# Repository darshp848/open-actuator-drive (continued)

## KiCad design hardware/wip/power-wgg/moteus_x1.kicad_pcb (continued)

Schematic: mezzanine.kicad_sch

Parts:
J_STACK1: DF40C-80DP-0.4V(51); Hirose_DF40C-80DP-0.4V_2x40-1MP_P0.4mm; MPN DF40C-80DP-0.4V(51)

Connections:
+3V: J_STACK1.73 (+3V), J_STACK1.75 (+3V), J_STACK1.76 (+3V), J_STACK1.77 (+3V); also elsewhere on the board
+5V: J_STACK1.53 (+5V), J_STACK1.54 (+5V), J_STACK1.55 (+5V), J_STACK1.56 (+5V); also elsewhere on the board
BRAKE_MON: J_STACK1.48 (BRAKE_MON)
CAN_H: J_STACK1.51 (CAN_H); also elsewhere on the board
CAN_L: J_STACK1.52 (CAN_L); also elsewhere on the board
ENC_OUTPUT_CS: J_STACK1.80 (ENC_OUTPUT_CS); also elsewhere on the board
ENC_ROTOR_CS: J_STACK1.30 (ENC_ROTOR_CS); also elsewhere on the board
ENC_SPI_MISO: J_STACK1.28 (ENC_SPI_MISO); also elsewhere on the board
ENC_SPI_MOSI: J_STACK1.29 (ENC_SPI_MOSI); also elsewhere on the board
ENC_SPI_SCK: J_STACK1.27 (ENC_SPI_SCK); also elsewhere on the board
GND: J_STACK1.3 (GND), J_STACK1.4 (GND), J_STACK1.6 (GND), J_STACK1.7 (GND), J_STACK1.10 (GND), J_STACK1.11 (GND), J_STACK1.14 (GND), J_STACK1.15 (GND), J_STACK1.18 (GND), J_STACK1.19 (GND), J_STACK1.22 (GND), J_STACK1.23 (GND), J_STACK1.25 (GND), J_STACK1.26 (GND), J_STACK1.31 (GND), J_STACK1.32 (GND), J_STACK1.35 (GND), J_STACK1.36 (GND), J_STACK1.39 (GND), J_STACK1.40 (GND), J_STACK1.43 (GND), J_STACK1.44 (GND), J_STACK1.49 (GND), J_STACK1.50 (GND), J_STACK1.57 (GND), J_STACK1.58 (GND), J_STACK1.62 (GND), J_STACK1.64 (GND), J_STACK1.66 (GND), J_STACK1.68 (GND), J_STACK1.72 (GND), J_STACK1.74 (GND), J_STACK1.78 (GND); also elsewhere on the board
/Current Sense/CUR1: J_STACK1.9 (CUR1); also elsewhere on the board
/Current Sense/CUR2: J_STACK1.8 (CUR2); also elsewhere on the board
/Current Sense/CUR3: J_STACK1.5 (CUR3); also elsewhere on the board
/Gate Driver/DRV8323_CS: J_STACK1.67 (DRV8323_CS); also elsewhere on the board
/Gate Driver/DRV8323_FAULT: J_STACK1.46 (DRV8323_FAULT); also elsewhere on the board
/Gate Driver/DRV8323_MISO: J_STACK1.65 (DRV8323_MISO); also elsewhere on the board
/Gate Driver/DRV8323_MOSI: J_STACK1.63 (DRV8323_MOSI); also elsewhere on the board
/Gate Driver/DRV8323_SCLK: J_STACK1.61 (DRV8323_SCLK); also elsewhere on the board
/Gate Driver/MOTOR1: J_STACK1.33 (MOTOR1); also elsewhere on the board
/Gate Driver/MOTOR2: J_STACK1.37 (MOTOR2); also elsewhere on the board
/Gate Driver/MOTOR3: J_STACK1.41 (MOTOR3); also elsewhere on the board
/Gate Driver/MOTOR_ENABLE: J_STACK1.45 (MOTOR_ENABLE); also elsewhere on the board
/Gate Driver/MOTOR_HIZ: J_STACK1.34 (MOTOR_HIZ); also elsewhere on the board
/VT Sense/VBAT_SENSE: J_STACK1.13 (VBAT_SENSE); also elsewhere on the board
/VT Sense/VTEMP_FET: J_STACK1.21 (VTEMP_FET); also elsewhere on the board
/VT Sense/VTEMP_MOT: J_STACK1.24 (VTEMP_MOT); also elsewhere on the board
/aux2/AUX2_C: J_STACK1.79 (AUX2_C); also elsewhere on the board

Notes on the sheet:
Fan functions share AUX2_C and ENC_OUTPUT_CS in the X1 reference. Do not fit R43/R44 with output encoder.
Odd contacts = logical A. Even contacts = logical B. Reserved pins are intentionally NC.
27 SCK / 28 MISO / 29 MOSI / 30 rotor CS now serve power-PCB encoders.
3V3 returns to power-board sensing. 5V feeds logic. Rail budgets and startup sequence remain open.

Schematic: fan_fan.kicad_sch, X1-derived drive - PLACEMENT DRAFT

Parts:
C82: 4.7uF; C_1206_3216Metric; MPN GRJ31CC72A475KE01K
FAN1: Conn_01x04_Pin; PinSocket_2x02_P2.54mm_Vertical; not fitted
R43, R44: 100; R_0402_1005Metric; MPN MF-RES-0402-100; not fitted

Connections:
+12V_GATE: C82.1, FAN1.2; also elsewhere on the board
ENC_OUTPUT_CS: R44.1; also elsewhere on the board
GND: C82.2, FAN1.1; also elsewhere on the board
unnamed: FAN1.3, R44.2
unnamed: FAN1.4, R43.2
/aux2/AUX2_C: R43.1; also elsewhere on the board

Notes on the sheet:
Split draft: original X1 circuit; actuator fit and final routing pending.
FAN1 is DNP. It now sits on +12V_GATE (sized for the gate driver, 100 mA stress): resize that rail before fitting a fan.
DNP FAN1, R43 and R44 with dual encoder configuration. GPIOs are shared.

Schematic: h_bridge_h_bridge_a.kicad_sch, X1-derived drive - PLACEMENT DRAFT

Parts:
C24: 0.1uF 100V; C_1206_3216Metric; MPN 12061C104KAT2A
D4: BAT41KFILM; SOD-523_STM; MPN BAT41KFILM
NT2, NT3: NetTie_2; NetTie-2_SMD_Pad0.2
Q1, Q2: ISC060N10NM6ATMA1; Infineon_PG-TDSON-8-FL_ISC060N10NM6; MPN ISC060N10NM6ATMA1
R14: 1mOhm; R_2512_6332Metric; MPN WSLF25121L000FEA
R51, R52: 2R; R_0603_1608Metric; MPN RC0603FR-072RL
R53, R54: 100k 1%; R_0402_1005Metric; MPN RC0402FR-07100KL
X1: Conn_01x01; POWER_M2.5

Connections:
/H Bridge A/SPX_Q: C24.2, NT2.2, Q2.1 (S), Q2.2 (S), Q2.3 (S), R14.1, R54.2
GNDPWR: D4.2, NT3.2, R14.2; also elsewhere on the board
unnamed: Q1.4 (G), R51.2, R53.1
unnamed: Q2.4 (G), R52.2, R54.1
V+: C24.1, Q1.5 (D); also elsewhere on the board
/Gate Driver/GHA: R51.1; also elsewhere on the board
/Gate Driver/GLA: D4.1, R52.1; also elsewhere on the board
/H Bridge A/OUTX: Q1.1 (S), Q1.2 (S), Q1.3 (S), Q2.5 (D), R53.2, X1.1; also elsewhere on the board
/H Bridge A/SXX_N: NT3.1; also elsewhere on the board
/H Bridge A/SXX_P: NT2.1; also elsewhere on the board

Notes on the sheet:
Split draft: original X1 circuit; actuator fit and final routing pending.

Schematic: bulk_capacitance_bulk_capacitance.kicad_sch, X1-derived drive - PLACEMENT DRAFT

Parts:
C45, C46, C47, C48, C49, C50, C51, C52, C53, C54, C55, C56, C57, C58, C59, C60, C61, C62, C63, C64, C65, C66, C67, C68, C69, C70, C71, C72, C73, C74, C75, C76, C77, C78, C79, C80: 4.7uF 100V; C_1206_3216Metric; MPN GRJ31CC72A475KE01K

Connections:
GNDPWR: C45.2, C46.2, C47.2, C48.2, C49.2, C50.2, C51.2, C52.2, C53.2, C54.2, C55.2, C56.2, C57.2, C58.2, C59.2, C60.2, C61.2, C62.2, C63.2, C64.2, C65.2, C66.2, C67.2, C68.2, C69.2, C70.2, C71.2, C72.2, C73.2, C74.2, C75.2, C76.2, C77.2, C78.2, C79.2, C80.2; also elsewhere on the board
V+: C45.1, C46.1, C47.1, C48.1, C49.1, C50.1, C51.1, C52.1, C53.1, C54.1, C55.1, C56.1, C57.1, C58.1, C59.1, C60.1, C61.1, C62.1, C63.1, C64.1, C65.1, C66.1, C67.1, C68.1, C69.1, C70.1, C71.1, C72.1, C73.1, C74.1, C75.1, C76.1, C77.1, C78.1, C79.1, C80.1; also elsewhere on the board

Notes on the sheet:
Split draft: original X1 circuit; actuator fit and final routing pending.

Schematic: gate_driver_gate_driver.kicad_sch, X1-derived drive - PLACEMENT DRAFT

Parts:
C18: 1uF; C_0603_1608Metric; MPN MF-CAP-0603-1uF
C19: 0.1uF 100V; C_0603_1608Metric; MPN GCJ188R72A104KA01D
C20: 1uF 16V; C_0402_1005Metric; MPN GRM155R61C105KA12D
C21, C22, C88, C89, C90: 1uF 25V; C_0603_1608Metric; MPN C1608X7R1E105K080AE
C85: 10uF 25V; C_0805_2012Metric; MPN GRM21BR61E106KA73L
C86: 1uF 100V; C_0805_2012Metric; MPN GCM21BC72A105KE36L
C87: 0.1uF 25V; C_0402_1005Metric; MPN GCM155R71E104KE02D
Q8: BSS138; SOT-23; MPN BSS138
R12, R13, R48, R49: 10k 1%; R_0402_1005Metric; MPN RC0402FR-0710KL
R50, R72: 100k 1%; R_0402_1005Metric; MPN RC0402FR-07100KL
U5: DRV8363RGZR; VQFN-48-1EP_7x7mm_P0.5mm_EP5.6x5.6mm_RGZ0048D; MPN DRV8363RGZR

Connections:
+3V: C18.1, C87.1, R12.1, R13.1, R48.1, U5.23 (VREF); also elsewhere on the board
+12V_GATE: C85.1, U5.30 (GVDD); also elsewhere on the board
/Gate Driver/ASCIN: R50.1, U5.29 (ASCIN)
/Gate Driver/BSTA: C88.1, U5.36 (BSTA)
/Gate Driver/BSTB: C89.1, U5.45 (BSTB)
/Gate Driver/BSTC: C90.1, U5.46 (BSTC)
/Gate Driver/CPH: C22.1, U5.33 (CPTH)
/Gate Driver/CPL: C22.2, U5.32 (CPTL)
/Gate Driver/DRVOFF: Q8.3 (D), R49.2, U5.9 (DRVOFF)
/Gate Driver/DVDD: C20.1, R49.1, U5.28 (DVDD)
/Gate Driver/NSLEEP: R48.2, U5.21 (nSLEEP)
/Gate Driver/VCP: C21.2, U5.34 (VCP)
GND: C18.2, C20.2, C85.2, C87.2, Q8.2 (S), R50.2, R72.2, U5.10 (AGND), U5.27 (GND); also elsewhere on the board
GNDPWR: C19.2, C86.2, U5.49 (PAD); also elsewhere on the board
V+: C19.1, C21.1, C86.1, U5.35 (VDRAIN); also elsewhere on the board
/Current Sense/CUR1: U5.24 (SOC); also elsewhere on the board
/Current Sense/CUR2: U5.25 (SOB); also elsewhere on the board
/Current Sense/CUR3: U5.26 (SOA); also elsewhere on the board
/Gate Driver/DRV8323_CS: U5.20 (nSCS); also elsewhere on the board
/Gate Driver/DRV8323_FAULT: R13.2, U5.22 (nFAULT); also elsewhere on the board
/Gate Driver/DRV8323_MISO: R12.2, U5.17 (SDO); also elsewhere on the board
/Gate Driver/DRV8323_MOSI: U5.18 (SDI); also elsewhere on the board
/Gate Driver/DRV8323_SCLK: U5.19 (SCLK); also elsewhere on the board
/Gate Driver/GHA: U5.38 (GHA); also elsewhere on the board
/Gate Driver/GHB: U5.43 (GHB); also elsewhere on the board
/Gate Driver/GHC: U5.48 (GHC); also elsewhere on the board
/Gate Driver/GLA: U5.39 (GLA); also elsewhere on the board
/Gate Driver/GLB: U5.42 (GLB); also elsewhere on the board
/Gate Driver/GLC: U5.1 (GLC); also elsewhere on the board
/Gate Driver/MOTOR1: U5.11 (INHA); also elsewhere on the board
/Gate Driver/MOTOR2: U5.13 (INHB); also elsewhere on the board
/Gate Driver/MOTOR3: U5.15 (INHC); also elsewhere on the board
/Gate Driver/MOTOR_ENABLE: Q8.1 (G), R72.1; also elsewhere on the board
/Gate Driver/MOTOR_HIZ: U5.12 (INLA), U5.14 (INLB), U5.16 (INLC); also elsewhere on the board
/H Bridge A/OUTX: C88.2, U5.37 (SHA); also elsewhere on the board
/H Bridge A/SXX_N: U5.4 (SNA); also elsewhere on the board
/H Bridge A/SXX_P: U5.3 (SPA), U5.40 (SLA); also elsewhere on the board
/H Bridge B/OUTX: C89.2, U5.44 (SHB); also elsewhere on the board
/H Bridge B/SXX_N: U5.6 (SNB); also elsewhere on the board
/H Bridge B/SXX_P: U5.5 (SPB), U5.41 (SLB); also elsewhere on the board
/H Bridge C/OUTX: C90.2, U5.47 (SHC); also elsewhere on the board
/H Bridge C/SXX_N: U5.8 (SNC); also elsewhere on the board
/H Bridge C/SXX_P: U5.2 (SLC), U5.7 (SPC); also elsewhere on the board

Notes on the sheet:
GVDD from +12V_GATE (separate gate rail, LT8631 U15 on the Power Input sheet). PAD (thermal) to GNDPWR, AGND/GND to GND (datasheet 7.3.1).
DRV8363 per SLVSHQ3 Table 7-1: CGVDD 10uF, CDVDD 1uF, CCPT_FLY 1uF, CVCP 1uF, RnFAULT 10k, CVREF 0.1uF, CVDRAIN 1uF, CBST 1uF
3x PWM: INHx = PWM, INLx = enable (MOTOR_HIZ). DRVOFF high = outputs off: R49 pulls it to DVDD, Q8 pulls it low only while MOTOR_ENABLE is high (off on +3V loss, reset or unplugged logic). ASCIN pulled low; SPI_ASC_EN is the firmware path (D06).

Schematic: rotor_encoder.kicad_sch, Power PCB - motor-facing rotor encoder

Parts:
C42: 1uF; C_0402_1005Metric; MPN MF-CAP-0402-1uF
C44: 0.1uF; C_0402_1005Metric; MPN MF-CAP-0402-0.1uF
R63: 10k; R_0603_1608Metric; MPN RC0603FR-0710KL
TP6: ROTOR_CAL; TestPoint_Pad_D1.0mm
U7: MT6835GT-STD-R; TSSOP-16_4.4x5mm_P0.65mm; MPN MT6835GT-STD-R

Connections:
+3V: C42.1, C44.1, U7.9 (VDD); also elsewhere on the board
ENC_ROTOR_CAL: R63.1, TP6.1, U7.4 (CAL_EN)
ENC_ROTOR_CS: U7.8 (CSN); also elsewhere on the board
ENC_SPI_MISO: U7.5 (MISO); also elsewhere on the board
ENC_SPI_MOSI: U7.6 (MOSI); also elsewhere on the board
ENC_SPI_SCK: U7.7 (SCK); also elsewhere on the board
GND: C42.2, C44.2, R63.2, U7.11 (TEST), U7.12 (VSS), U7.13 (TEST_EN); also elsewhere on the board

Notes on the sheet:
U7 is now an MT6835 (user decision 2026-10-24), wired like U9: SPI mode 3 shared with the output sensor; CS = ENC_ROTOR_CS (pull-up R47 on the output-encoder sheet).

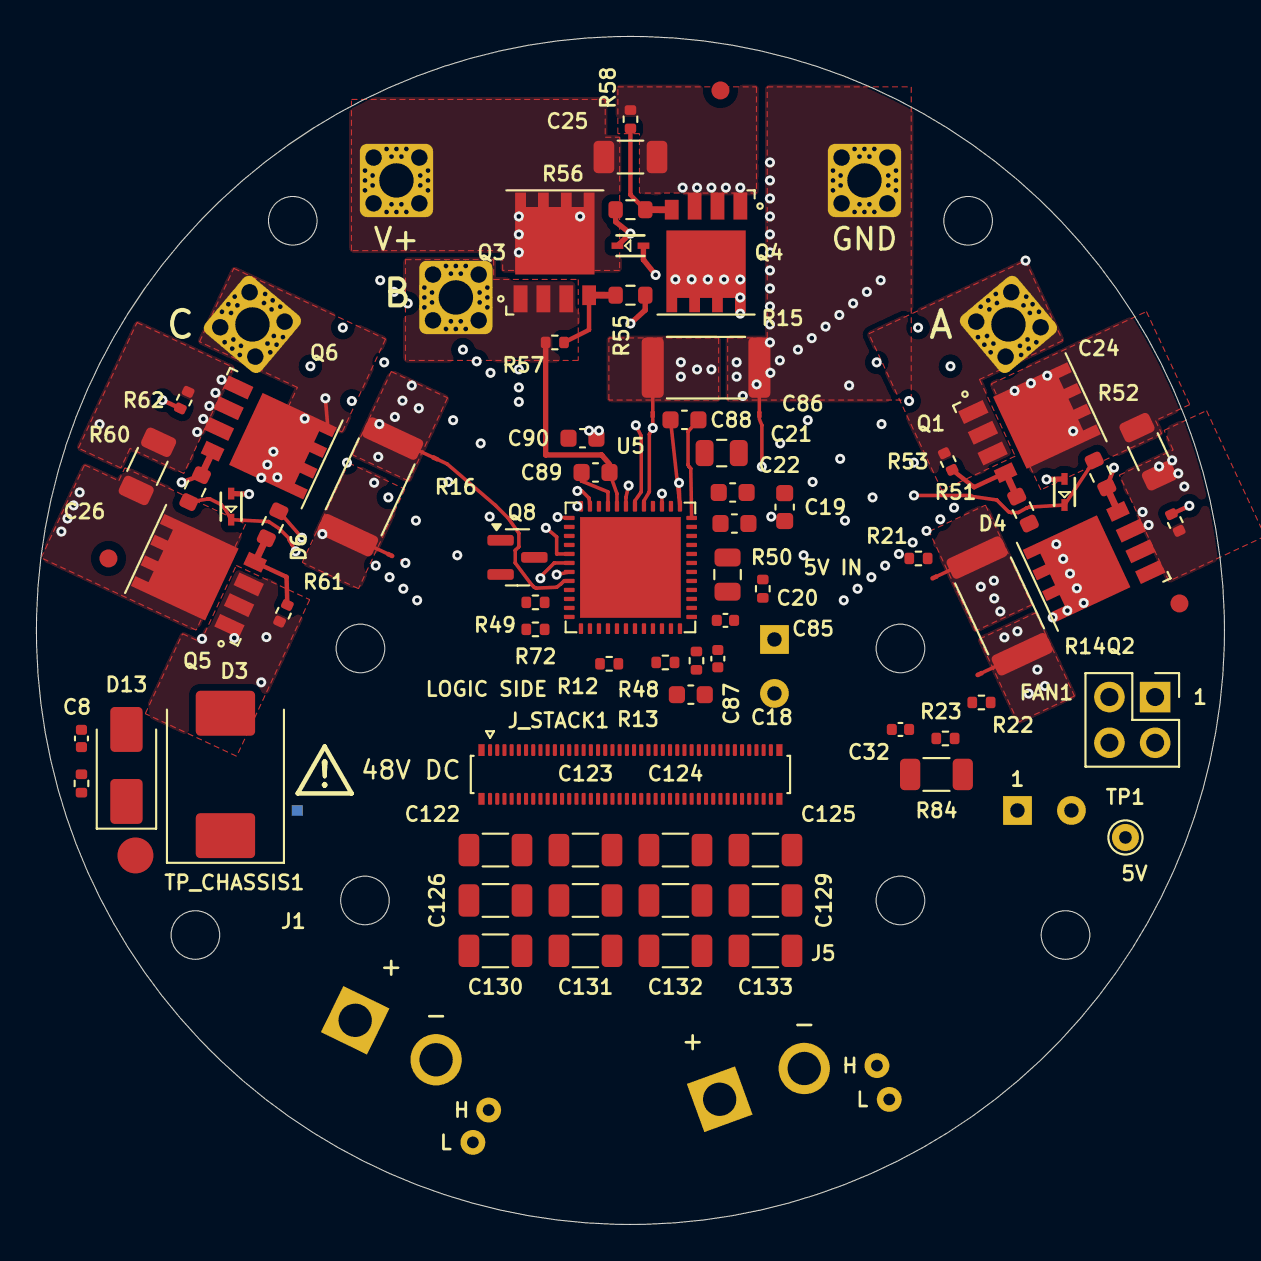
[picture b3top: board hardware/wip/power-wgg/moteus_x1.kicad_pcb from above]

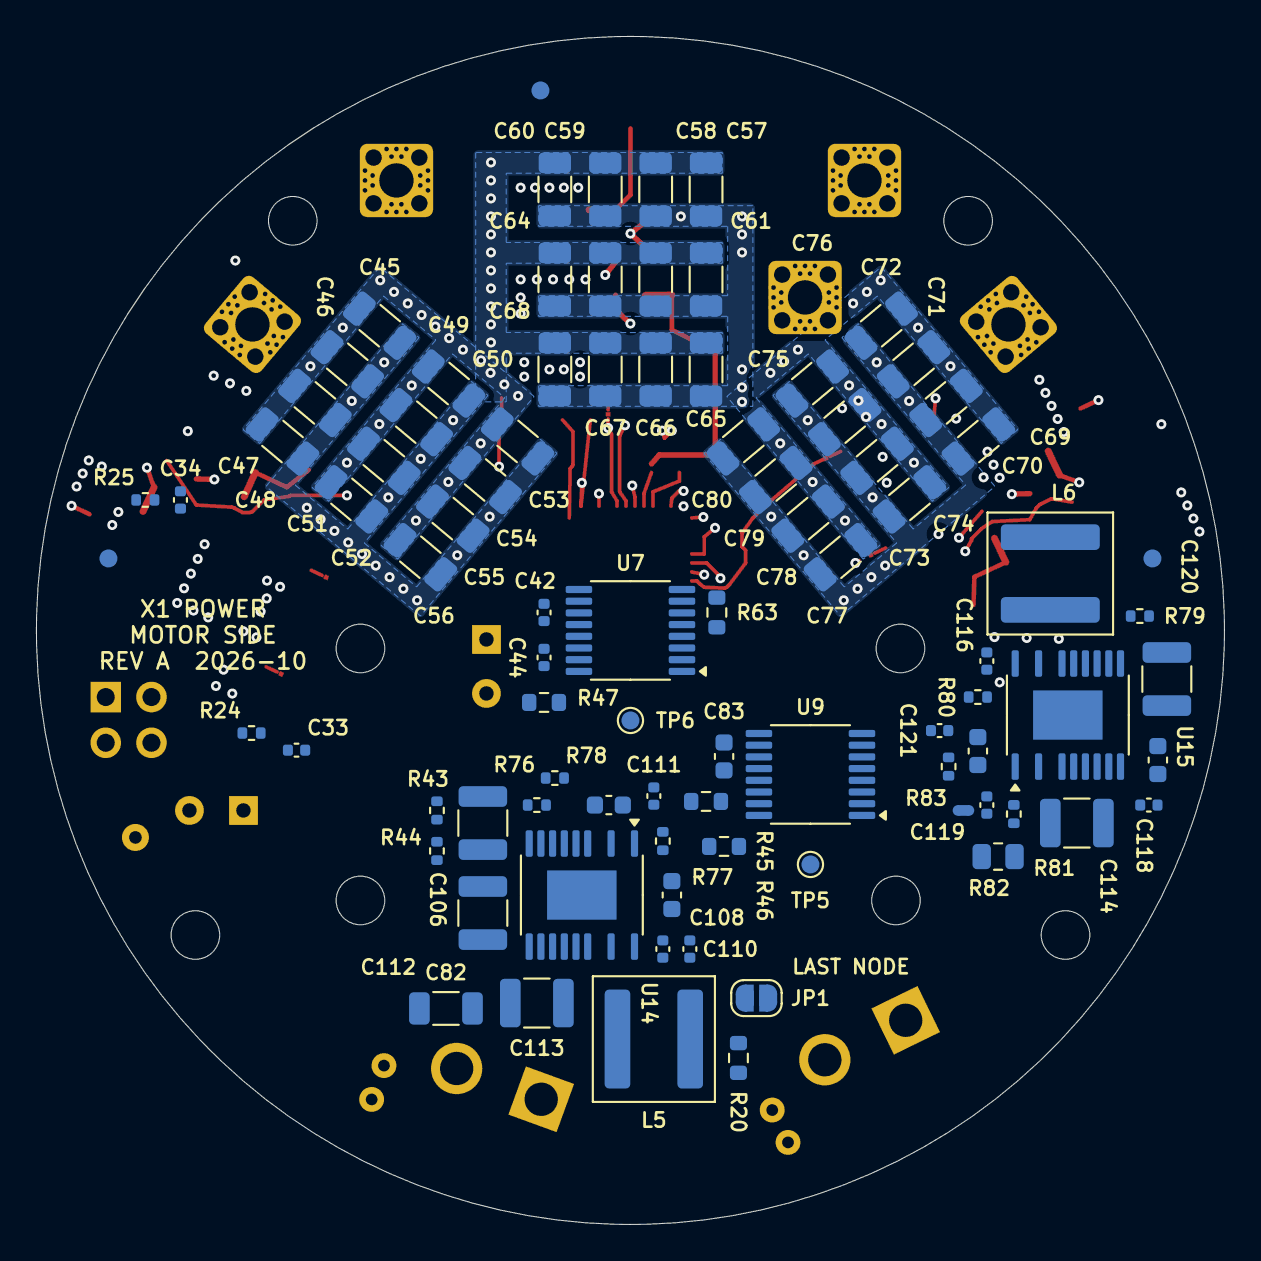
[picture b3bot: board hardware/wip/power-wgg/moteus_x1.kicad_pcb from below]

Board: 6 copper layers, 66.0 x 66.0 mm, 185 parts (88 on the bottom side), 87 nets.

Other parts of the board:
FID_B1, FID_B2, FID_B3: Fiducial_1mm_Mask2mm
FID_F1, FID_F2, FID_F3: Fiducial_1mm_Mask2mm

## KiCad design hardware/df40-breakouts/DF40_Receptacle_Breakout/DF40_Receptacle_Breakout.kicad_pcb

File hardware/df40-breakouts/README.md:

# X1 stack DF40 breakouts

Two bench breakouts for the X1 two-story stack. The stack has one
board-to-board connector, J_STACK1, a Hirose DF40 80-contact pair at 0.4 mm
pitch:

| Board | Part | Side |
| --- | --- | --- |
| Common_Logic | DF40HC(3.0)-80DS-0.4V receptacle | bottom |
| Power_Reference (WGG) and Power_P96 | DF40C-80DP-0.4V header | top |

The other connectors in the X1 projects (XT30/XT90, JST GH/ZR/PH, 1.27 and
2.54 mm pin headers) are cable or debug connectors, not mezzanines.

No off-the-shelf DF40 80-pin to 0.1" breakout was found (2026-11-01 search:
distributor listings, Tindie, OSH Park; the only DF40 breakout found is a
30-pin OSH Park project), so these are custom.

## The boards

| Project | Connector | Use |
| --- | --- | --- |
| `DF40_Header_Breakout` | DF40C-80DP-0.4V on top | The logic board plugs onto it exactly as it plugs onto a power board. Bring up or probe the logic board alone. |
| `DF40_Receptacle_Breakout` | DF40HC(3.0)-80DS-0.4V on the bottom | Plugs onto a power board in place of the logic board. Drive or probe a power board from a bench MCU. |

Every DF40 contact gets one 0.1" through-hole point. J2 (2x20) carries the odd
row and J3 (2x20) the even row: J2 pin k is DF40 pin 2k-1 and J3 pin k is DF40
pin 2k. Each pin is labelled on the silkscreen with its DF40 pin number and net.
[`pinout.json`](pinout.json) has the full map.

Mechanical fit:

- The connector uses the stack boards' own land patterns (copied into
  `X1_Breakout.pretty`), at the same position, side and orientation as the board
  it stands in for. The generator asserts pad 1 lands where it does on the stack.
- H1/H2 are the two spacer positions common to all three stack boards
  ((135,115) and (165,115) in stack coordinates). With 3 mm spacers there they
  fix orientation, so the DF40 cannot be mated 180 degrees out. The other stack
  holes sit in the fan-out and are omitted; remove those spacers first.
- Near the connector the outline stays inside the logic board's footprint and
  clears P96's 5V IN pads. It covers P96's FAN1 socket, as the logic board
  itself does; that clash is open on the stack and both fit once FAN1 moves.
- The headers sit at least 2 mm beyond the rim of both power boards, so no
  through-hole pin lands over a power board. The tongue that crosses the rim
  rides 3 mm above the power board. Checked against P96 and Power_Reference:
  only parts under 2.6 mm tall are under it. Re-check this for any new power
  board.

Electrical:

- 2 layers, 1.6 mm, about 100 x 80 mm, ground pour on both sides. The even
  DF40 row fans out below the connector to two staggered via rows, so no via
  sits at the 0.4 mm pitch. All bends are 45 degrees. About 330 tented
  0.6/0.3 mm stitching vias on a 2.5 mm grid tie the two ground pours together
  wherever the pour has room on both layers.
- Every rule is inside JLCPCB's standard 2-layer process with no surcharge
  (jlcpcb.com/capabilities/pcb-capabilities, read 2026-11-02): trace/space
  0.127/0.127 mm (limit 0.10), vias 0.6/0.3 mm (0.15 mm annular ring), via hole
  to track at least 0.2 mm, copper to edge 0.3 mm (limit 0.2), silkscreen text
  1.0 mm with 0.17 mm lines. KiCad's DRC rules are set to these values.
- Signal integrity (hand estimates): with no plane under the 0.4 mm-pitch
  buses, neighbouring traces couple about 24% near-end to a ~1 ns edge. Near-end
  crosstalk scales with how much of the edge fits in the ~0.5-1 ns of coupled
  length, so with 10 ns edges it falls to roughly 2-3% (under 0.1 V from a
  3.3 V signal). Drive these lines with the STM32 GPIO speed set to low or
  medium and keep SPI to a few MHz. Every analog line (CUR1-3, VBAT_SNS,
  VTEMP_*) has GND traces on both sides; the signal-to-signal neighbours are
  the DRV SPI group, ENC_SCK/MOSI, ENC_MISO/ROT_CS, DRV_FAULT/BRAKE_MON and
  CAN_H/CAN_L next to +5V. No line needs controlled impedance. A four-layer design with ground inner layers was estimated at about 5% coupling.
- The four +5V and four +3V contacts are tied together between the DF40 pad
  rows, as they are on the stack boards. Each contact is rated 0.3 A, and each
  0.127 mm trace carries about the same, so keep each rail under about 1 A
  through the breakout.
- Reserved contacts (`RSV_*`) are broken out but are unconnected on the stack
  boards today.

## Status

KiCad 10.0 DRC: 0 violations, 0 unconnected, schematic parity clean. ERC:
0 violations. Not fabricated, not mated with real parts, and not yet run
through JLCPCB's online DFM check.

[Header Gerber and drill ZIP](../../fab/df40-breakouts/DF40_Header_Breakout/DF40_Header_Breakout-gerbers.zip)
and [receptacle Gerber and drill ZIP](../../fab/df40-breakouts/DF40_Receptacle_Breakout/DF40_Receptacle_Breakout-gerbers.zip).
The design uses a two-layer, 1.6 mm stackup. Review the [fabrication notes](../../fab/)
and [parts list](bom.csv) before preparing an order.

The breakouts inherit the stack's open item: DF40 pad numbering versus Hirose's
mating view has not been checked against the datasheet. They copy the stack
footprints exactly, so they agree with the stack whichever way that resolves.

## Regenerating

```
"%LOCALAPPDATA%/Programs/KiCad/10.0/bin/python.exe" generate.py
```

[`generate.py`](generate.py) reads J_STACK1 from the three stack boards, fails if
their pinouts disagree, and rewrites both breakout projects in place. Run it in a disposable checkout to compare
its outputs. It only reads the stack
boards. Routing is generated by the script; Freerouting could not escape the
0.4 mm pitch.

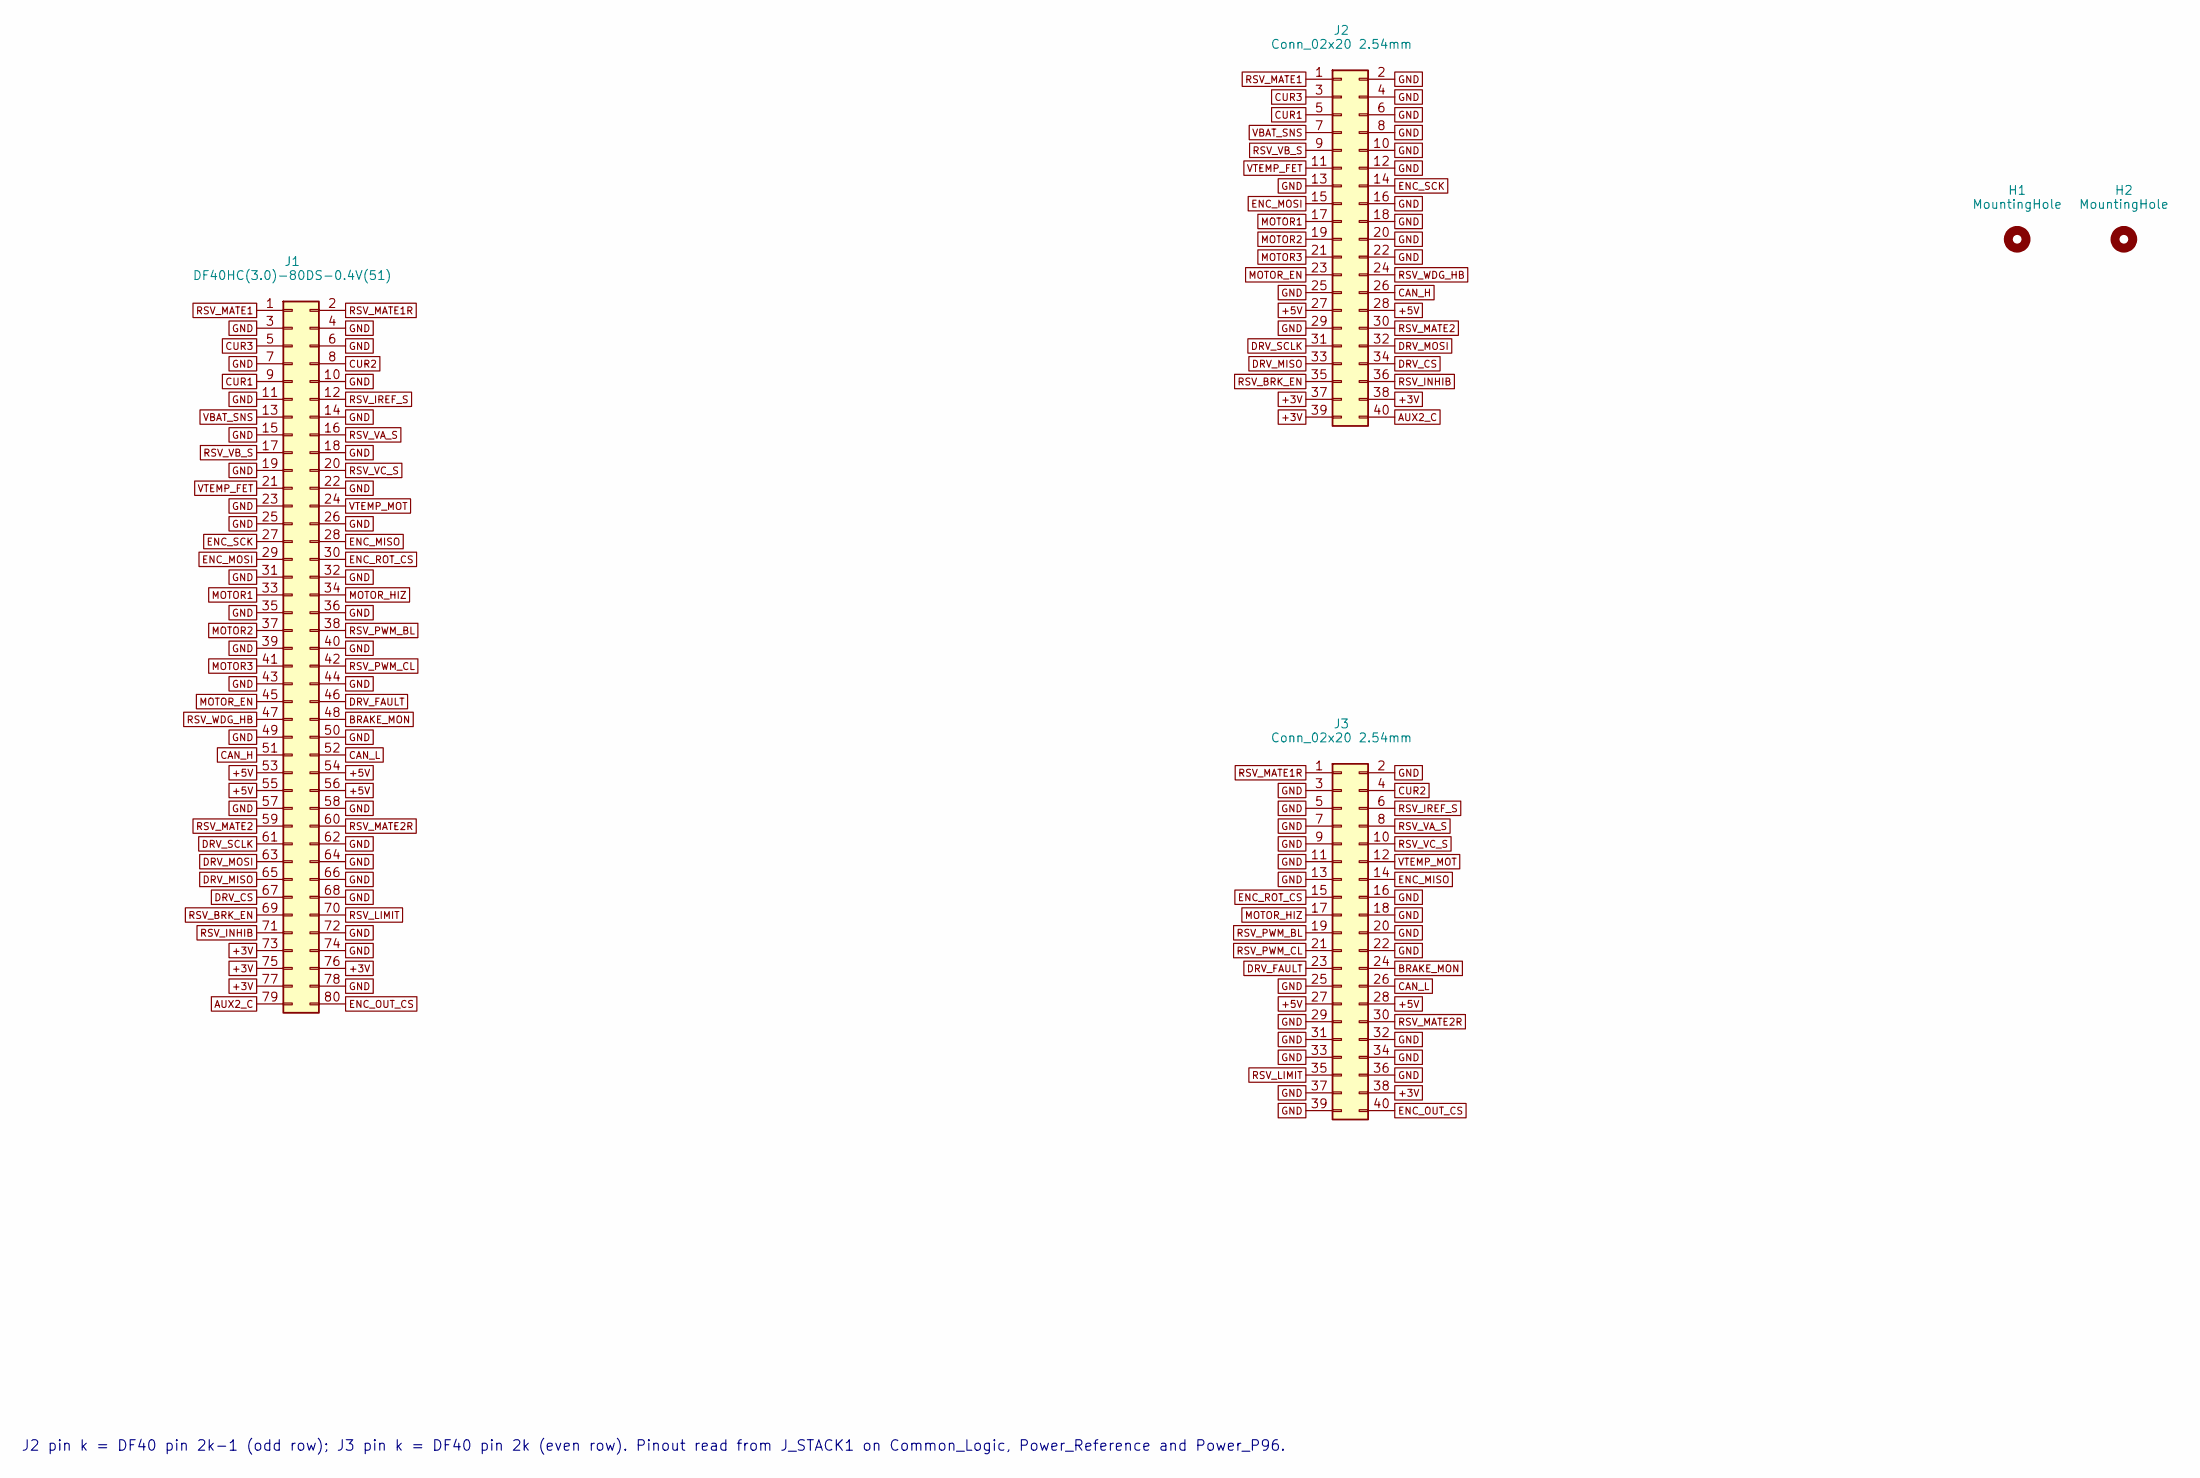
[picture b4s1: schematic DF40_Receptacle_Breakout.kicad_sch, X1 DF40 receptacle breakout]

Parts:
H1, H2: MountingHole; MountingHole_2.7mm_M2.5
J1: DF40HC(3.0)-80DS-0.4V(51); Hirose_DF40HC(3.0)-80DS-0.4V_2x40_P0.4mm
J2, J3: Conn_02x20 2.54mm; PinHeader_2x20_P2.54mm_Vertical

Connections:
+3V: J1.73, J1.75, J1.76, J1.77, J2.37, J2.38, J2.39, J3.38
+5V: J1.53, J1.54, J1.55, J1.56, J2.27, J2.28, J3.27, J3.28
AUX2_C: J1.79, J2.40
BRAKE_MON: J1.48, J3.24
CAN_H: J1.51, J2.26
CAN_L: J1.52, J3.26
CUR1: J1.9, J2.5
CUR2: J1.8, J3.4
CUR3: J1.5, J2.3
DRV_CS: J1.67, J2.34
DRV_FAULT: J1.46, J3.23
DRV_MISO: J1.65, J2.33
DRV_MOSI: J1.63, J2.32
DRV_SCLK: J1.61, J2.31
ENC_MISO: J1.28, J3.14
ENC_MOSI: J1.29, J2.15
ENC_OUT_CS: J1.80, J3.40
ENC_ROT_CS: J1.30, J3.15
ENC_SCK: J1.27, J2.14
GND: J1.3, J1.4, J1.6, J1.7, J1.10, J1.11, J1.14, J1.15, J1.18, J1.19, J1.22, J1.23, J1.25, J1.26, J1.31, J1.32, J1.35, J1.36, J1.39, J1.40, J1.43, J1.44, J1.49, J1.50, J1.57, J1.58, J1.62, J1.64, J1.66, J1.68, J1.72, J1.74, J1.78, J2.2, J2.4, J2.6, J2.8, J2.10, J2.12, J2.13, J2.16, J2.18, J2.20, J2.22, J2.25, J2.29, J3.2, J3.3, J3.5, J3.7, J3.9, J3.11, J3.13, J3.16, J3.18, J3.20, J3.22, J3.25, J3.29, J3.31, J3.32, J3.33, J3.34, J3.36, J3.37, J3.39
MOTOR1: J1.33, J2.17
MOTOR2: J1.37, J2.19
MOTOR3: J1.41, J2.21
MOTOR_EN: J1.45, J2.23
MOTOR_HIZ: J1.34, J3.17
RSV_BRK_EN: J1.69, J2.35
RSV_INHIB: J1.71, J2.36
RSV_IREF_S: J1.12, J3.6
RSV_LIMIT: J1.70, J3.35
RSV_MATE1: J1.1, J2.1
RSV_MATE1R: J1.2, J3.1
RSV_MATE2: J1.59, J2.30
RSV_MATE2R: J1.60, J3.30
RSV_PWM_BL: J1.38, J3.19
RSV_PWM_CL: J1.42, J3.21
RSV_VA_S: J1.16, J3.8
RSV_VB_S: J1.17, J2.9
RSV_VC_S: J1.20, J3.10
RSV_WDG_HB: J1.47, J2.24
VBAT_SNS: J1.13, J2.7
VTEMP_FET: J1.21, J2.11
VTEMP_MOT: J1.24, J3.12

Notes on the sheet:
J2 pin k = DF40 pin 2k-1 (odd row); J3 pin k = DF40 pin 2k (even row). Pinout read from J_STACK1 on Common_Logic, Power_Reference and Power_P96.

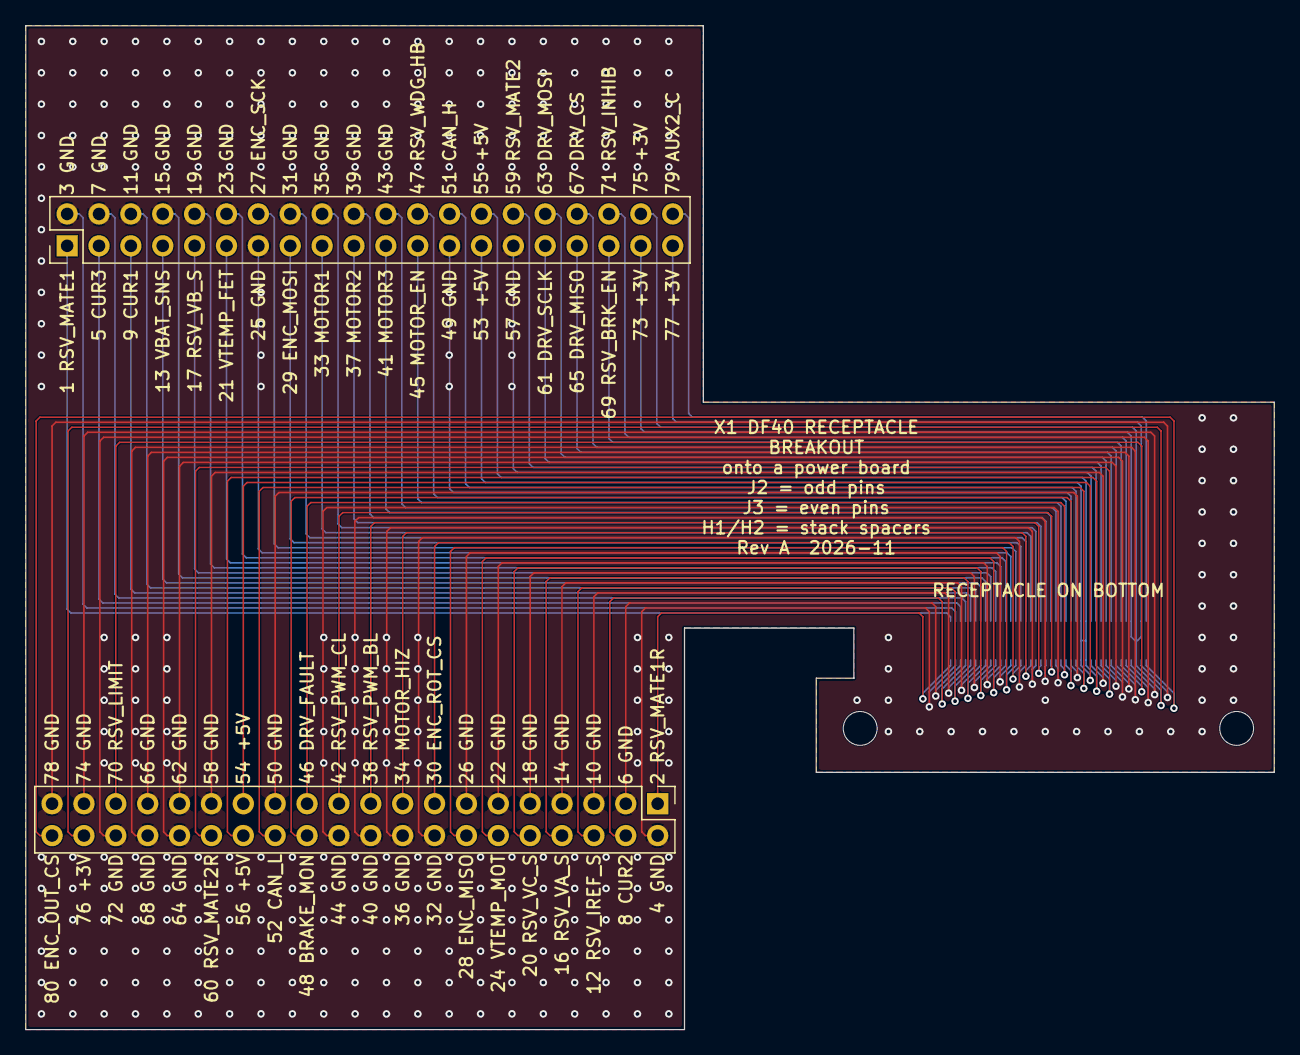
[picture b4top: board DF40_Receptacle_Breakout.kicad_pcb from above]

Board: 2 copper layers, 99.5 x 80.0 mm, 5 parts (1 on the bottom side), 42 nets.

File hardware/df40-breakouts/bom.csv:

Board,Ref,Qty per board,Manufacturer,MPN,DigiKey PN,DigiKey stock 2026-11-02,Unit price (qty 1)
DF40_Header_Breakout,J1,1,Hirose,DF40C-80DP-0.4V(51),cut tape (search MPN),25224,$1.93
DF40_Receptacle_Breakout,J1,1,Hirose,DF40HC(3.0)-80DS-0.4V(51),26-DF40HC(3.0)-80DS-0.4V(51)CT-ND,4743,$3.13
Both,J2 J3,2,Sullins,PRPC020DAAN-RC,35-PRPC020DAAN-RC-ND,5823,$0.95

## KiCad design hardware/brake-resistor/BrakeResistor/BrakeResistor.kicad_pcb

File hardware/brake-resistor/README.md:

# X1 brake resistor board (rev B)

The 2.5 ohm load for the [support board](../support-board/)'s brake chopper.
The current Rev B layout is a 190 × 38 mm strip with four heatsinks in one row.

## What it is

| | |
|---|---|
| Bank | 4 x Vishay LTO100 10 ohm in parallel = 2.5 ohm (same value the support board and system model assume) |
| Cooling | Each resistor screwed to its own Ohmite RA-T2X-64E board-level heatsink (3.1 C/W natural), with silicone grease |
| Thermostat | Sensata Airpax 67L085P, normally closed, opens at 85 +/- 5 C. Its bracket is plastic, so it is isolated. It shares R4's M3 screw on the far face of HS4's web. |
| J1 | Two 2.0 mm wire pads, 8 mm pitch, the same land as support J4. 1 = BUS+, 2 = BRK_SW. Use a 16 AWG pair. |
| J2 | JST PH 2-pin to support J6 (PH to PH lead). 1 = TH_OPEN, 2 = support GND. |
| PCB | 190 × 38 mm, 2 layers, 1.6 mm, 1 oz nominal. BUS+ is a plane on top and BRK_SW a plane on the bottom, so the chopper loop is two parallel plates. |
| Cost | About $62 in parts for one board at qty 1 (see [bom.csv](bom.csv); all in stock at DigiKey on 2026-11-02) plus the PCB |

Mount the board flat with the heatsink fins vertical. The heatsinks have a nominal
4 mm gap between adjacent end fins. The five M3 holes and both connectors sit
along the long edge.

## Thermal sizing for the earlier layout

[brake_sizing.py](brake_sizing.py) models the earlier two-by-two heatsink layout. Its output is in
[checks/brake_sizing-output.txt](checks/brake_sizing-output.txt).

The strip's smaller gaps change airflow. The estimates below have no hardware
validation and do not establish ratings for the strip.

The model puts 1.3 kW across the bank while the chopper conducts. Each burst lasts
only about 0.17 ms (52 mJ per resistor, 5 % of the LTO100 cold single-pulse
limit). Averaged over time, the bank dissipates the regenerated power and no
more. So the 1.3 kW figure does not size anything. What sizes the bank is:

- **Earlier layout estimate: 41 W average at 40 C ambient** (61 W at 25 C). That is the
  power at which the heatsinks reach 80 C, the lowest point at which the
  thermostat may open. The resistors are well inside their rating there:
  case 90 C, element 106 C. The LTO100 would allow 56 W each at that case
  temperature.
- **Events: limited by the resistor element, not the heatsink.** The LTO100's
  thick-film element has very little thermal mass. With the bank already at
  its continuous rating:

  | Event energy | Highest bank power | Shortest duration |
  |---|---|---|
  | 25 J | 664 W | 0.04 s |
  | 50 J | 370 W | 0.14 s |
  | 100 J | 251 W | 0.40 s |
  | 150 J | 203 W | 0.74 s |
  | 300 J | 154 W | 1.95 s |

  A cold bank takes roughly twice these powers.

Regen profiles checked (all assumptions, none measured):

| Case | Profile | Load | Result |
|---|---|---|---|
| A1 | P96 arm, lift6 cycle from the system model: 28 J every 3.5 s | 8 W avg | fits |
| A2 | P96 arm, fast pick-and-place: J1 and J2 each lower 6 kg at 3 rad/s (GIM8115 limit about 3.8 rad/s at 48 V), 70 W each for 0.52 s, every 2 s | 36 W avg | fits, sinks 76 C |
| A3 | P96 gates-off fall, J1+J2+J4 (brake-resistor-check-20261025.md), starting hot from A2 | 140 J in 0.65 s | fits, element 160 C |
| A4 | P96 arm e-stop from speed, starting hot from A2 | about 30 J in 0.1 s | fits |
| W1 | 3 x WGG8108-8, gait-like braking: each 160 W for 0.1 s per 1 s step, two in phase | 32 W avg | fits |
| W2 | 3 x WGG8108-8 stopped from 819 rpm (Kv x 50.4 V) at the full 1.3 kW chopper rate: 106 J of rotor energy plus the 50 J `regen_event_j` target | 156 J in 0.12 s | **too hot**. It fits if firmware caps total regen at about 200 W, which is a 0.75 s stop. |
| W3 | 1 x WGG8108-8 braking continuously at its nominal 10.2 Nm and 390 rpm (a dyno or winch load) | 341 W avg | **not supported** by any passive board this size |
| F1 | Support-board forced discharge when RUN opens: 3 mF from 54 V | 5 J | fits |

Assumptions:
- GIM8115/GIM8108 data from `system_model/openarm_params.m`.
- The WGG8108-8 is taken at its 24 V catalog data. Rotor inertia is unpublished, so 1.5e-4 kg m2 is assumed.
- Gear efficiency 0.9 (0.85 for WGG). All regen goes to the brake, with nothing credited to the supply (requirements.json).
- 40 C ambient.
- Heatsink rise is read off Ohmite's curve and derated 15 % for four sinks in a 2 x 2 block.
- The LTO100 transient impedance is fitted to Vishay's energy curve, conservatively at 0.2 s.

## What this needs from the rest of the system

1. **Firmware must cap regen power.** The table above is the contract. Hard
   stops of the WGG motors from high speed are the case that breaks it. Above
   about 650 W total for more than about 40 ms, an LTO100 element overheats,
   and thick film usually fails open. With the bank open, the next regen
   event takes the bus past the 80 V parts.
2. **The thermostat does not stop regen** (pushing back on the support-board
   design here). On the support board an open J6 only blocks the forced
   discharge (Q6). The heatsinks can keep heating
   with the thermostat open. TH_OPEN should also reach the
   controllers so they stop regenerating, or drop RUN.
3. **A source above 57.1 V would burn the bank.** The LM5069 overvoltage
   lockout lets the source back on below 57.6 V. That is above the 57.1 V
   chopper threshold, so a supply set to about 57.2-59 V (a misset bench PSU,
   for example) holds the chopper on at 1.3 kW. From hot the bank survives
   about 6 ms of that. Either move the OVLO re-enable below 55 V or add a
   maximum on-time or duty limit to the chopper. This is a support-board
   change, so it is not made here.
4. If the WGG application really needs sustained braking (W3), cooling is the
   lever: Ohmite rates the same sink at 1.0 C/W in 200 LFM of air, about three
   times the continuous rating. The other option is an aluminium-housed
   wirewound resistor on a plate. Those have far more thermal mass for events,
   for example a single Yageo AHA50AFB-2R5 or Ohmite HS50 2R5 (both in stock).

## Open items

- The resistor and thermostat now use 3.0 mm and 1.8 mm round plated holes.
  Dry-fit HS4, its resistor, the thermostat and the shared fastener before
  soldering. Check lead shoulder clearance, clamping and insulation.
- Front-side copper keepouts follow the nominal metal base profiles with
  margin. Check the as-built sink-to-pad clearance and verify insulation
  around the floating sink pins. The 3D models are simplified envelopes.
- Enclosure airflow, thermal behavior and the support-board interlock
  remain to be verified. Fabricator DFM and first-article fit are open.

## Files

- [KiCad project](BrakeResistor/BrakeResistor.kicad_pro) and [parts list](bom.csv).
- [Gerber and drill ZIP](../../fab/brake-resistor/BrakeResistor/BrakeResistor-gerbers.zip)
  and [schematic PDF](../../fab/brake-resistor/BrakeResistor/BrakeResistor-schematic.pdf).
- [ERC report](checks/BrakeResistor-erc.json) and
  [DRC and parity report](checks/BrakeResistor-drc.json) for the strip.
- [Generator for the earlier 120 × 86 mm layout](generate.py). Running it
  in this folder overwrites the strip layout. Use the KiCad project as the
  editable source for the strip.

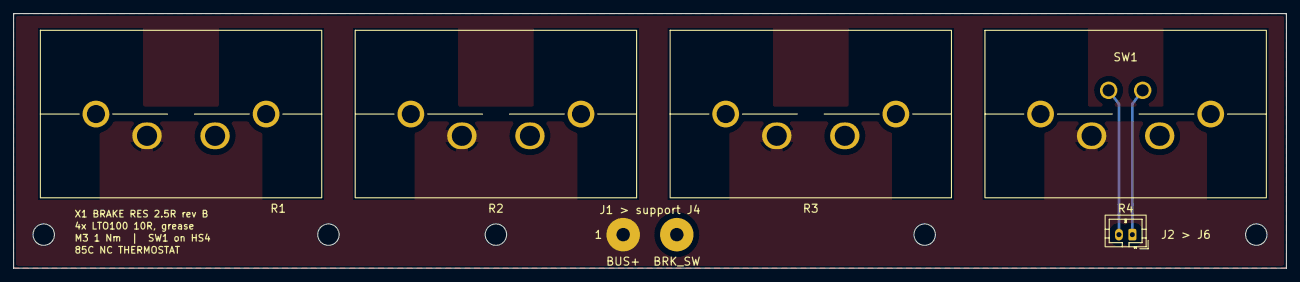
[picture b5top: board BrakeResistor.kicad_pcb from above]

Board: 2 copper layers, 190.0 x 38.0 mm, 12 parts (0 on the bottom side), 4 nets.

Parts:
H1, H2, H3, H4, H5: M3; MountingHole_3.2mm_M3
J1: to support J4; PowerWire_P8
J2: to support J6 (JST PH); JST_PH_B2B-PH-K_1x02_P2.00mm_Vertical
R1, R2, R3, R4: 10R LTO100; LTO100_on_Ohmite_RA-T2X-64E
SW1: 67L085P NC opens 85C; Airpax_67L_TO-220-2_on_RA-T2X_web

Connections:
BRK_SW: J1.2, R1.2, R2.2, R3.2, R4.2
BUS+: J1.1, R1.1, R2.1, R3.1, R4.1
TH_GND: J2.2, SW1.1
TH_OPEN: J2.1, SW1.2

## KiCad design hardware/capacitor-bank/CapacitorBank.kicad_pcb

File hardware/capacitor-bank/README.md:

# External capacitor bank

This two-layer, 101.6 × 25.4 mm board puts twelve 130 µF, 80 V capacitors
across the DC bus for 1,560 µF nominal, with a 10 kΩ bleeder. The
[KiCad project](CapacitorBank.kicad_pro) includes the custom footprints and a
simplified capacitor body. See the [parts list](bom.csv), [schematic
PDF](../../fab/capacitor-bank/CapacitorBank/CapacitorBank-schematic.pdf) and
[Gerber and drill ZIP](../../fab/capacitor-bank/CapacitorBank/CapacitorBank-gerbers.zip).

The layout is routed. KiCad 10.0.7 reported zero DRC findings, unconnected
items, schematic mismatches and ERC findings. Footprint fit and polarity,
assembly, bus ripple, inrush, discharge time and temperature rise still need
verification on hardware.

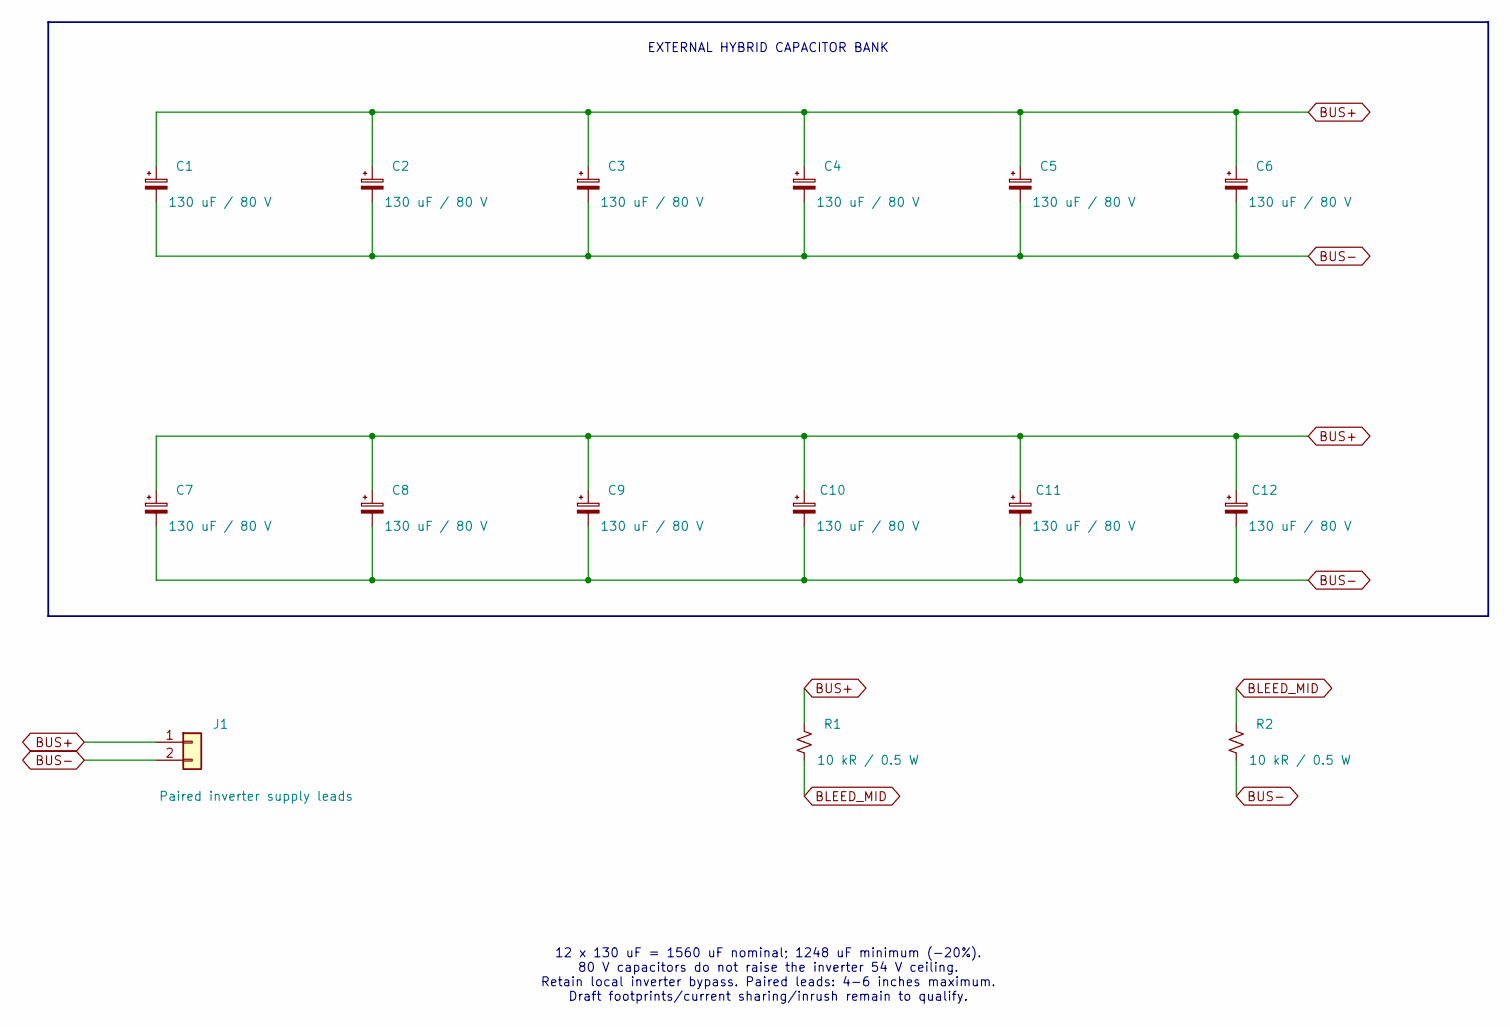
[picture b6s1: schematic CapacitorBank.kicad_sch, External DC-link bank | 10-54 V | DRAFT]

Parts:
C1, C2, C3, C4, C5, C6, C7, C8, C9, C10, C11, C12: 130 uF / 80 V; TDK_B40910_10x16p5_DRAFT; MPN B40910A0137M000
J1: Paired inverter supply leads; PowerWire_P8
R1, R2: 10 kR / 0.5 W; Bleeder_2512

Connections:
BLEED_MID: R1.2, R2.1
BUS+: C1.1, C2.1, C3.1, C4.1, C5.1, C6.1, C7.1, C8.1, C9.1, C10.1, C11.1, C12.1, J1.1, R1.1
BUS-: C1.2, C2.2, C3.2, C4.2, C5.2, C6.2, C7.2, C8.2, C9.2, C10.2, C11.2, C12.2, J1.2, R2.2

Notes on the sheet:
12 x 130 uF = 1560 uF nominal; 1248 uF minimum (-20%). 80 V capacitors do not raise the inverter 54 V ceiling. Retain local inverter bypass. Paired leads: 4-6 inches maximum. Draft footprints/current sharing/inrush remain to qualify.
EXTERNAL HYBRID CAPACITOR BANK

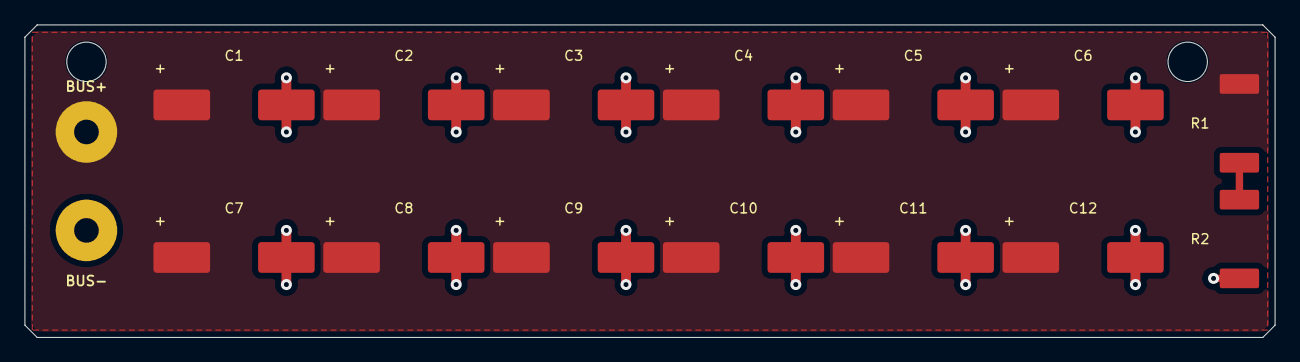
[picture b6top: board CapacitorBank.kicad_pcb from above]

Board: 2 copper layers, 101.6 x 25.4 mm, 17 parts (0 on the bottom side), 3 nets.

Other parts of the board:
H1, H2: (no value)
